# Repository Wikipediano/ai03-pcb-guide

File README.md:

# ai03-pcb-guide
 These are the files of my follow-through of ai03's PCB design guide

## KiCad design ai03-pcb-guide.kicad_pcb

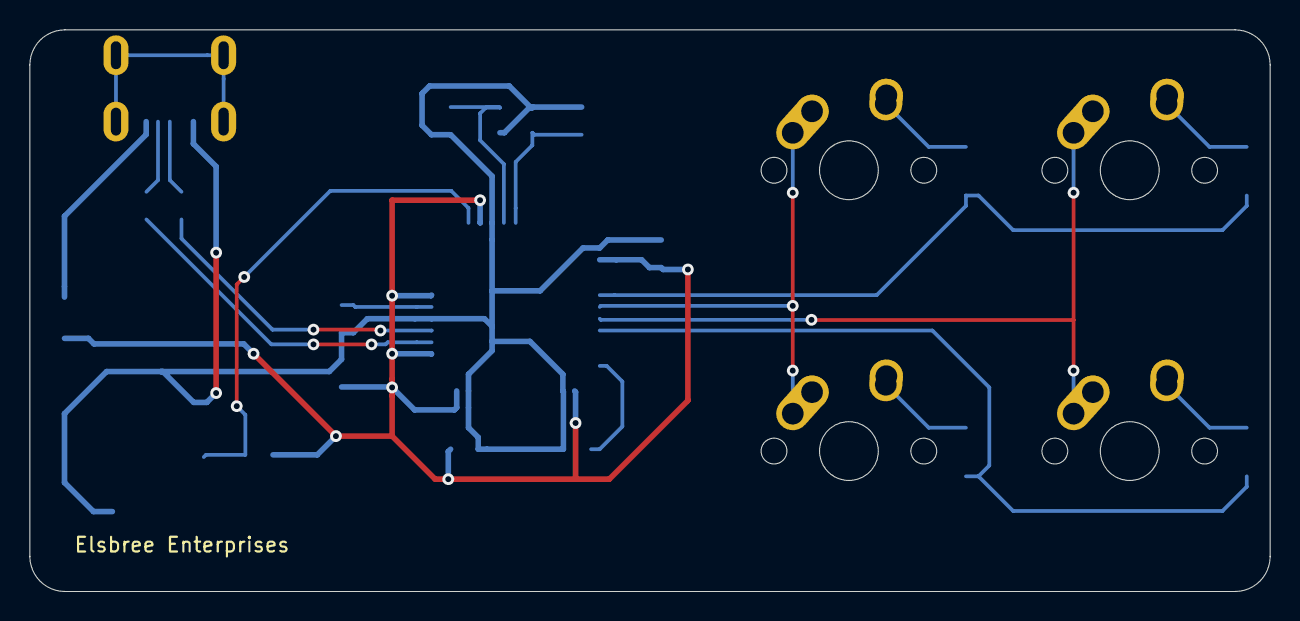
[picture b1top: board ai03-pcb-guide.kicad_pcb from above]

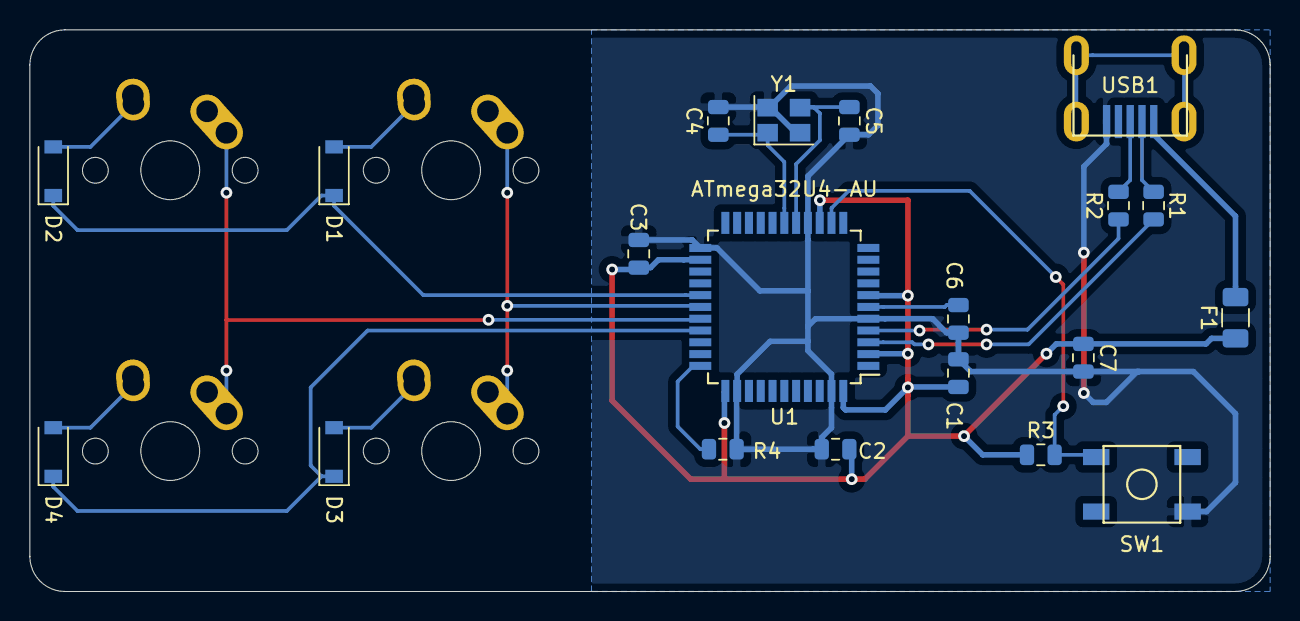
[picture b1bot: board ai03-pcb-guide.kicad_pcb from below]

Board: 2 copper layers, 84.1 x 38.1 mm, 24 parts (20 on the bottom side), 20 nets.

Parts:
C1, C2, C3: 0.1uF; C_0805_2012Metric
C4, C5: 22pF; C_0805_2012Metric
C6: 1uF; C_0805_2012Metric
C7: 10uF; C_0805_2012Metric
D1, D2, D3, D4: D_Small; D_SOD-123
F1: 500mA; Fuse_1206_3216Metric
MX1, MX2, MX3, MX4: MX-NoLED; MX-1U-NoLED
R1, R2: 22; R_0805_2012Metric
R3, R4: 10k; R_0805_2012Metric
SW1: SW_Push; SKQG-1155865
U1: ATmega32U4-AU; TQFP-44_10x10mm_P0.8mm
USB1: Molex-0548190589
Y1: 10MHz; Crystal_SMD_3225-4Pin_3.2x2.5mm

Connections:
+5V: C1.1, C2.1, C3.1, C7.1, F1.1, R3.1, U1.2, U1.7, U1.14, U1.24, U1.34, U1.44
COL0: MX1.1, MX3.1, U1.28
COL1: MX2.1, MX4.1, U1.29
D+: R2.2, USB1.3
D-: R1.2, USB1.4
GND: C1.2, C2.2, C3.2, C4.2, C5.2, C6.2, C7.2, R4.1, SW1.1, U1.5, U1.15, U1.23, U1.35, U1.43, USB1.1, Y1.2, Y1.4
unnamed: C4.1, U1.17, Y1.1
unnamed: C5.1, U1.16, Y1.3
unnamed: C6.1, U1.6
unnamed: D1.2, MX1.2
unnamed: D2.2, MX2.2
unnamed: D3.2, MX3.2
unnamed: D4.2, MX4.2
unnamed: R1.1, U1.3
unnamed: R2.1, U1.4
unnamed: R3.2, SW1.2, U1.13
unnamed: R4.2, U1.33
ROW0: D1.1, D2.1, U1.27
ROW1: D3.1, D4.1, U1.30
VCC: F1.2, USB1.5

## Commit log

2020-08-06 Add submodules
2020-08-06 Added libraries to project
2020-08-06 Revert "Added libraries to project"
    This reverts commit 0d22d17496c3ca70bc4218468cb0b519ccb9c8e1.
2020-08-06 Revert "Revert "Added libraries to project""
    This reverts commit 6d7f87d851a5407fd831b6c43f2a91dacb012f3f.
2020-08-06 Shematic & footprint associations
2020-08-07 PCB layout & traces
2020-08-07 Generated Gerber files and finalized pcb
2020-08-07 Remade gerbers
